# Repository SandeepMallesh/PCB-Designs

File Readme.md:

# PCB-Designs 

--------------------------------------------------------------------------------------------------------

** ALL PROJECTS ARE DESIGNED WITH KICAD ** : 𝕂𝕚𝕔𝕒𝕕

KICAD SOFTWARE LINK : 

** WINDOWS ** : https://www.kicad.org/download/windows/

** MAC OS **  : https://www.kicad.org/download/macos/

** LINUX **   : https://www.kicad.org/download/linux/

---------------------------------------------------------------------------------------------------------

𝕯𝖊𝖘𝖎𝖌𝖓𝖊𝖉 𝖇𝖞 ✍
✌𝓐𝓳𝓪𝔂𝓜𝓪𝓵𝓵𝓮𝓼𝓱✌
---------------------------------------------------------------------------------------------------------

███████████████████████████▀███████████████████████████████████
█▄─▄▄▀█▄─▄▄─█─▄▄▄▄█▄─▄█─▄▄▄▄█▄─▀█▄─▄█▄─▄▄─█▄─▄▄▀███▄─▄─▀█▄─█─▄█
██─██─██─▄█▀█▄▄▄▄─██─██─██▄─██─█▄▀─███─▄█▀██─██─████─▄─▀██▄─▄██
▀▄▄▄▄▀▀▄▄▄▄▄▀▄▄▄▄▄▀▄▄▄▀▄▄▄▄▄▀▄▄▄▀▀▄▄▀▄▄▄▄▄▀▄▄▄▄▀▀▀▀▄▄▄▄▀▀▀▄▄▄▀▀
███████████████████████████████████████████████████████████████████
██▀▄─████▄─▄██▀▄─██▄─█─▄█▄─▀█▀─▄██▀▄─██▄─▄███▄─▄███▄─▄▄─█─▄▄▄▄█─█─█
██─▀─██─▄█─███─▀─███▄─▄███─█▄█─███─▀─███─██▀██─██▀██─▄█▀█▄▄▄▄─█─▄─█
▀▄▄▀▄▄▀▄▄▄▀▀▀▄▄▀▄▄▀▀▄▄▄▀▀▄▄▄▀▄▄▄▀▄▄▀▄▄▀▄▄▄▄▄▀▄▄▄▄▄▀▄▄▄▄▄▀▄▄▄▄▄▀▄▀▄▀

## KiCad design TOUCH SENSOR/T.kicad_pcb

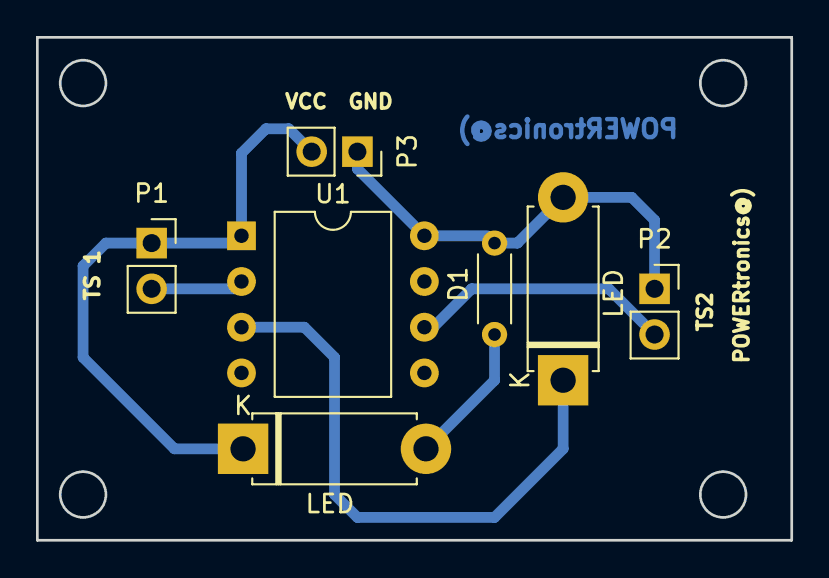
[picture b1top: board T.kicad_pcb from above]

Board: 2 copper layers, 41.9 x 27.9 mm, 7 parts (0 on the bottom side), 6 nets.

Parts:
D1: LED; D_5W_P10.16mm_Horizontal
LED: LED; D_5W_P10.16mm_Horizontal
LED#2: R; R_Axial_DIN0204_L3.6mm_D1.6mm_P5.08mm_Horizontal
P1, P2, P3: CONN_01X02; PinSocket_1x02_P2.54mm_Vertical
U1: NE555; DIP-8_W10.16mm

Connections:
GND: LED.1, P1.1, P3.2, U1.1
unnamed: D1.1, U1.3
unnamed: LED.2, LED#2.2
unnamed: P1.2, U1.2
unnamed: P2.2, U1.6
VCC: D1.2, LED#2.1, P2.1, P3.1, U1.8

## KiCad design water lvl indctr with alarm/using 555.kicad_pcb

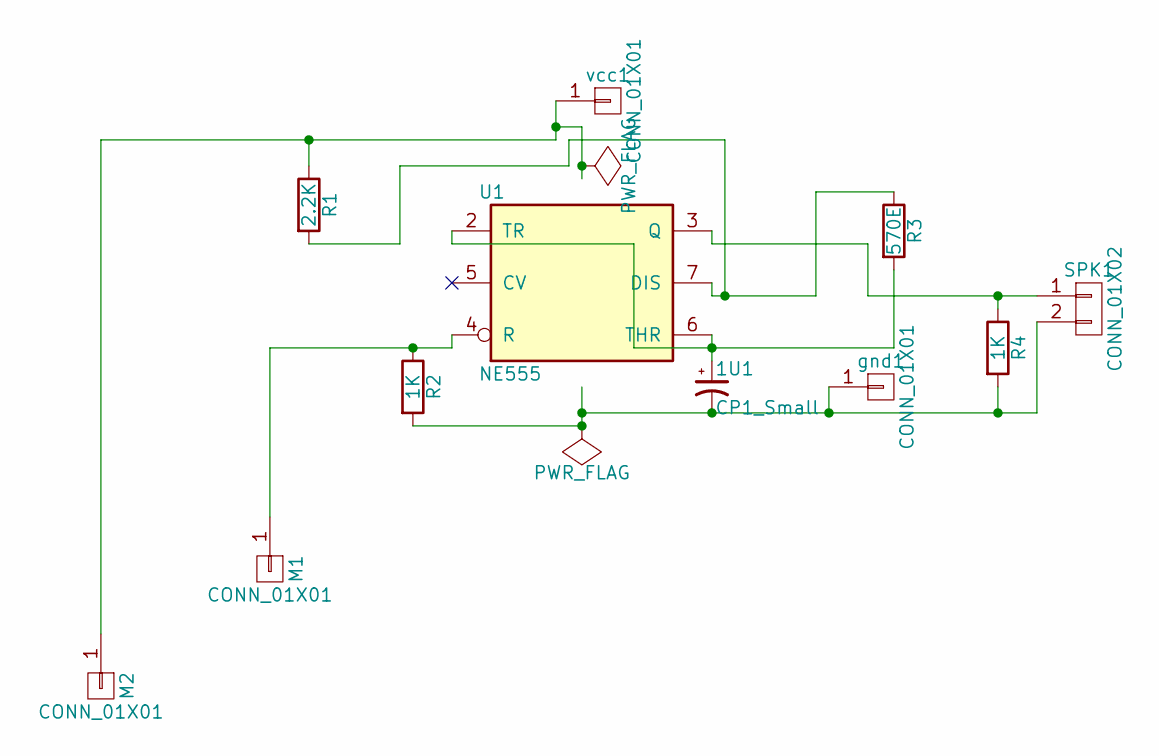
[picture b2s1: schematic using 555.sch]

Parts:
1U1: CP1_Small; C_Disc_D3.0mm_W1.6mm_P2.50mm
M1, M2: CONN_01X01; Pin_Header_Straight_1x01_Pitch2.54mm
R1: 2.2K; R_Axial_DIN0204_L3.6mm_D1.6mm_P5.08mm_Horizontal
R2, R4: 1K; R_Axial_DIN0204_L3.6mm_D1.6mm_P5.08mm_Horizontal
R3: 570E; R_Axial_DIN0204_L3.6mm_D1.6mm_P5.08mm_Horizontal
SPK1: CONN_01X02; Pin_Header_Straight_1x02_Pitch2.54mm
U1: NE555; DIP-8_W7.62mm
gnd1: CONN_01X01; Pin_Header_Straight_1x01_Pitch2.54mm
vcc1: CONN_01X01; Pin_Header_Straight_1x01_Pitch2.54mm

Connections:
GND: 1U1.2, R2.2, R4.2, SPK1.2, U1.1 (GND), gnd1.1
unnamed: 1U1.1, R3.2, U1.2 (TR), U1.6 (THR)
unnamed: M1.1, R2.1, U1.4 (R)
unnamed: R1.2, R3.1, U1.7 (DIS)
unnamed: R4.1, SPK1.1, U1.3 (Q)
VCC: M2.1, R1.1, U1.8 (VCC), vcc1.1

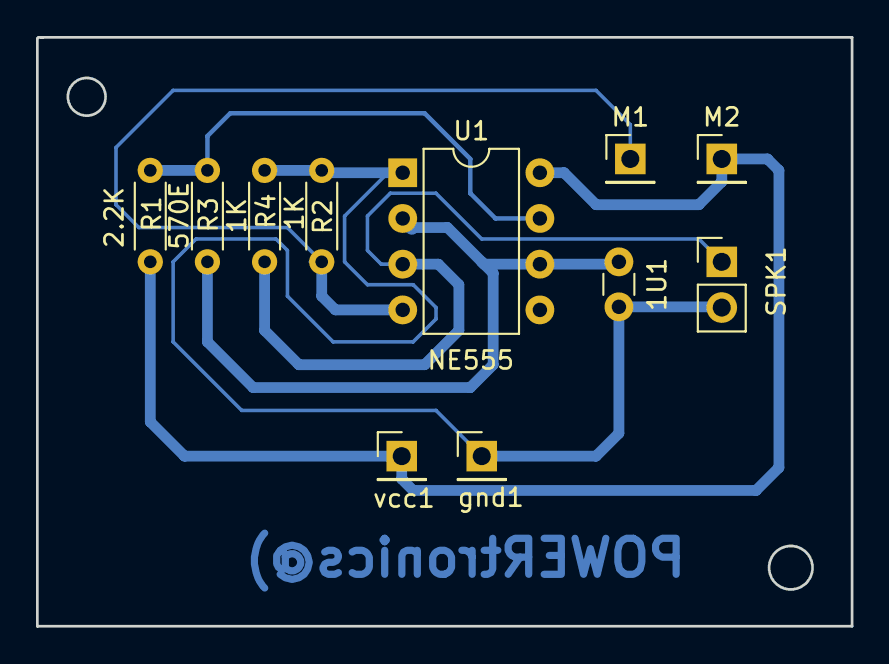
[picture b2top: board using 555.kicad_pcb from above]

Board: 2 copper layers, 45.3 x 32.7 mm, 11 parts (0 on the bottom side), 6 nets.

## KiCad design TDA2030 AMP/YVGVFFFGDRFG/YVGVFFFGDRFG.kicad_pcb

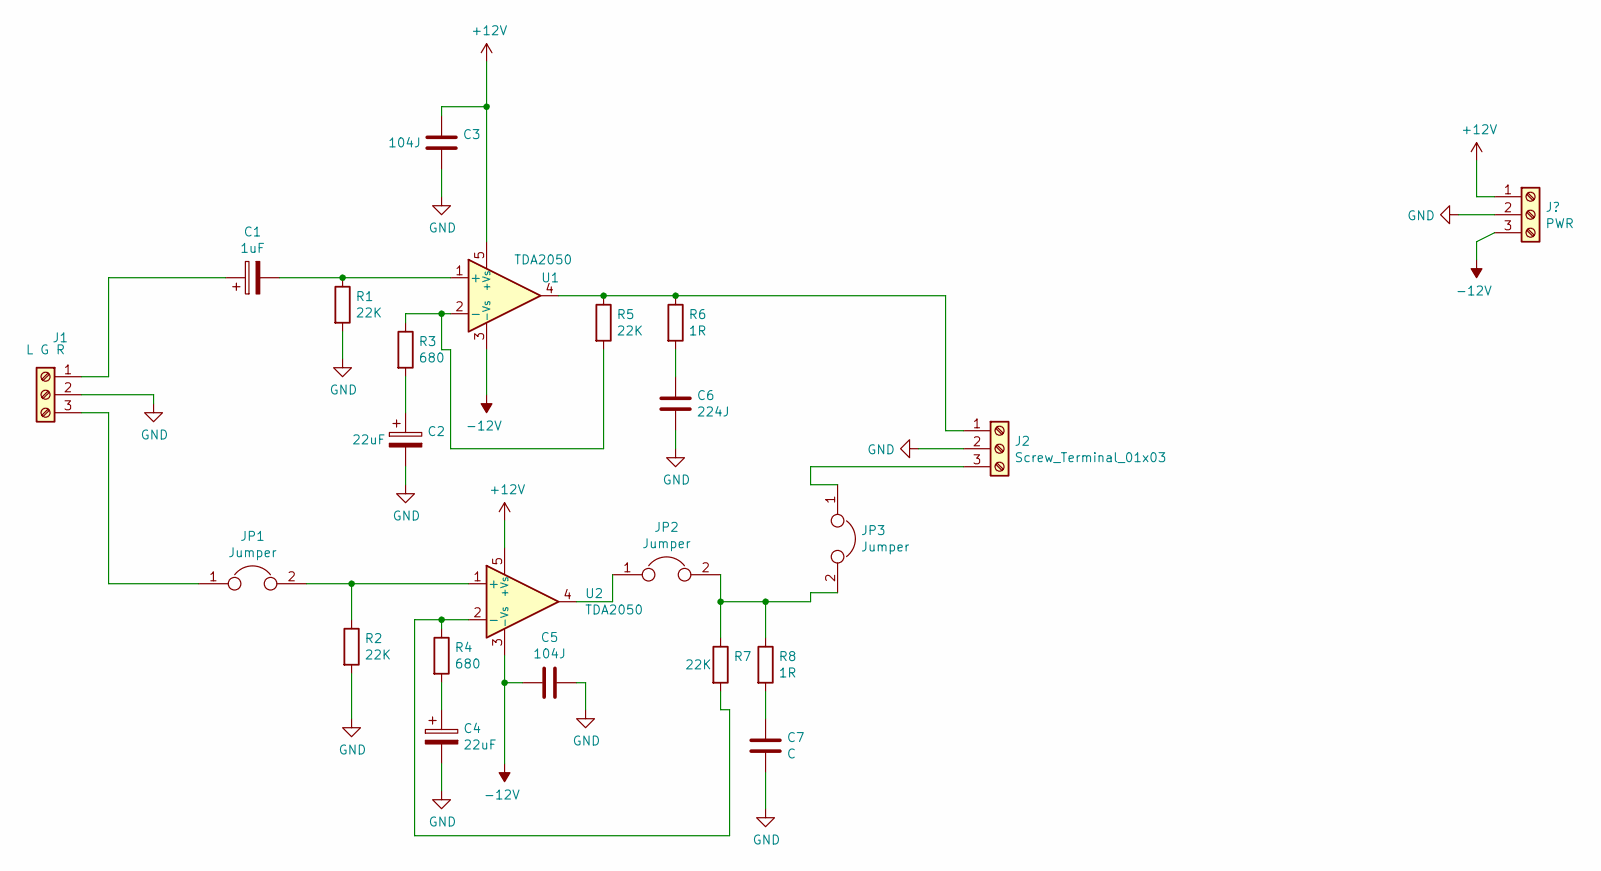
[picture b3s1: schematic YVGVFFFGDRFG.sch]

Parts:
C1: 1uF; CP_Radial_D4.0mm_P2.00mm
C2, C4: 22uF; CP_Radial_D4.0mm_P2.00mm
C3, C5: 104J; C_Rect_L4.6mm_W2.0mm_P2.50mm_MKS02_FKP02
C6: 224J; C_Rect_L4.6mm_W2.0mm_P2.50mm_MKS02_FKP02
C7: C; C_Rect_L4.0mm_W2.5mm_P2.50mm
J1: L G R; TerminalBlock_bornier-3_P5.08mm
J2: Screw_Terminal_01x03; TerminalBlock_bornier-3_P5.08mm
JP1, JP2, JP3: Jumper; TestPoint_2Pads_Pitch2.54mm_Drill0.8mm
R1, R2, R5, R7: 22K; R_Axial_DIN0204_L3.6mm_D1.6mm_P5.08mm_Horizontal
R3, R4: 680; R_Axial_DIN0204_L3.6mm_D1.6mm_P5.08mm_Horizontal
R6, R8: 1R; R_Axial_DIN0204_L3.6mm_D1.6mm_P5.08mm_Horizontal
U1, U2: TDA2050; TO-220-5_Vertical_StaggeredType1

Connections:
+12V: C3.1, U1.5 (+Vs), U2.5 (+Vs)
-12V: C5.2, U1.3 (-Vs), U2.3 (-Vs)
GND: C2.2, C3.2, C4.2, C5.1, C6.2, C7.2, J1.2, J2.2, R1.2, R2.2
unnamed: C1.1, J1.1
unnamed: C1.2, R1.1, U1.1 (+)
unnamed: C2.1, R3.2
unnamed: C4.1, R4.2
unnamed: C6.1, R6.2
unnamed: C7.1, R8.2
unnamed: J1.3, JP1.1
unnamed: J2.1, R5.1, R6.1, U1.4
unnamed: J2.3, JP3.1
unnamed: JP1.2, R2.1, U2.1 (+)
unnamed: JP2.1, U2.4
unnamed: JP2.2, JP3.2, R7.1, R8.1
unnamed: R3.1, R5.2, U1.2 (-)
unnamed: R4.1, R7.2, U2.2 (-)

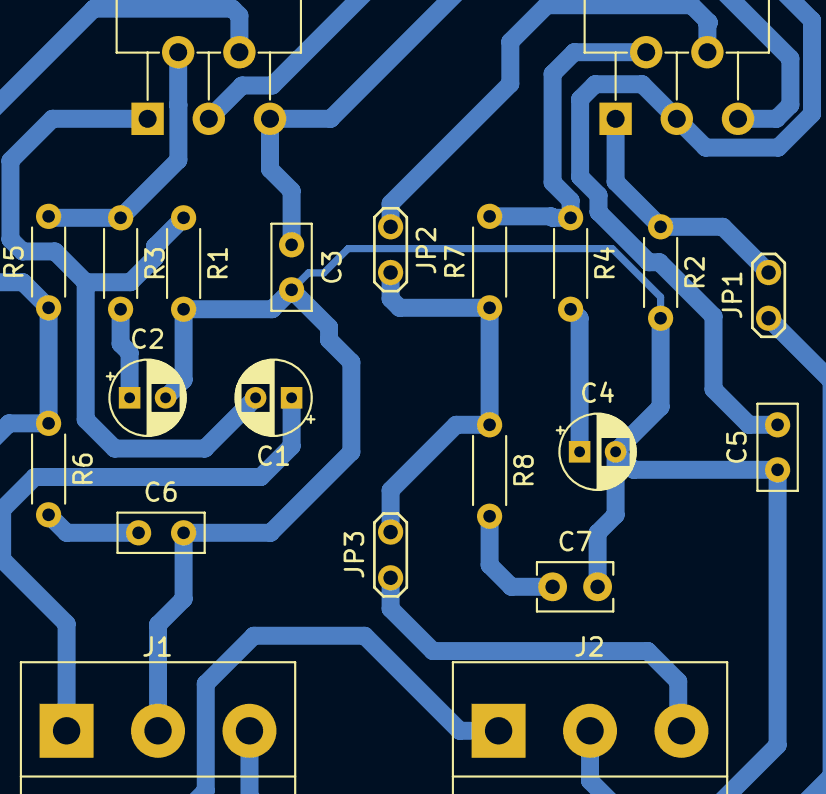
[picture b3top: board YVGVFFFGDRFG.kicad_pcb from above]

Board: 2 copper layers, 22 parts (0 on the bottom side), 17 nets.

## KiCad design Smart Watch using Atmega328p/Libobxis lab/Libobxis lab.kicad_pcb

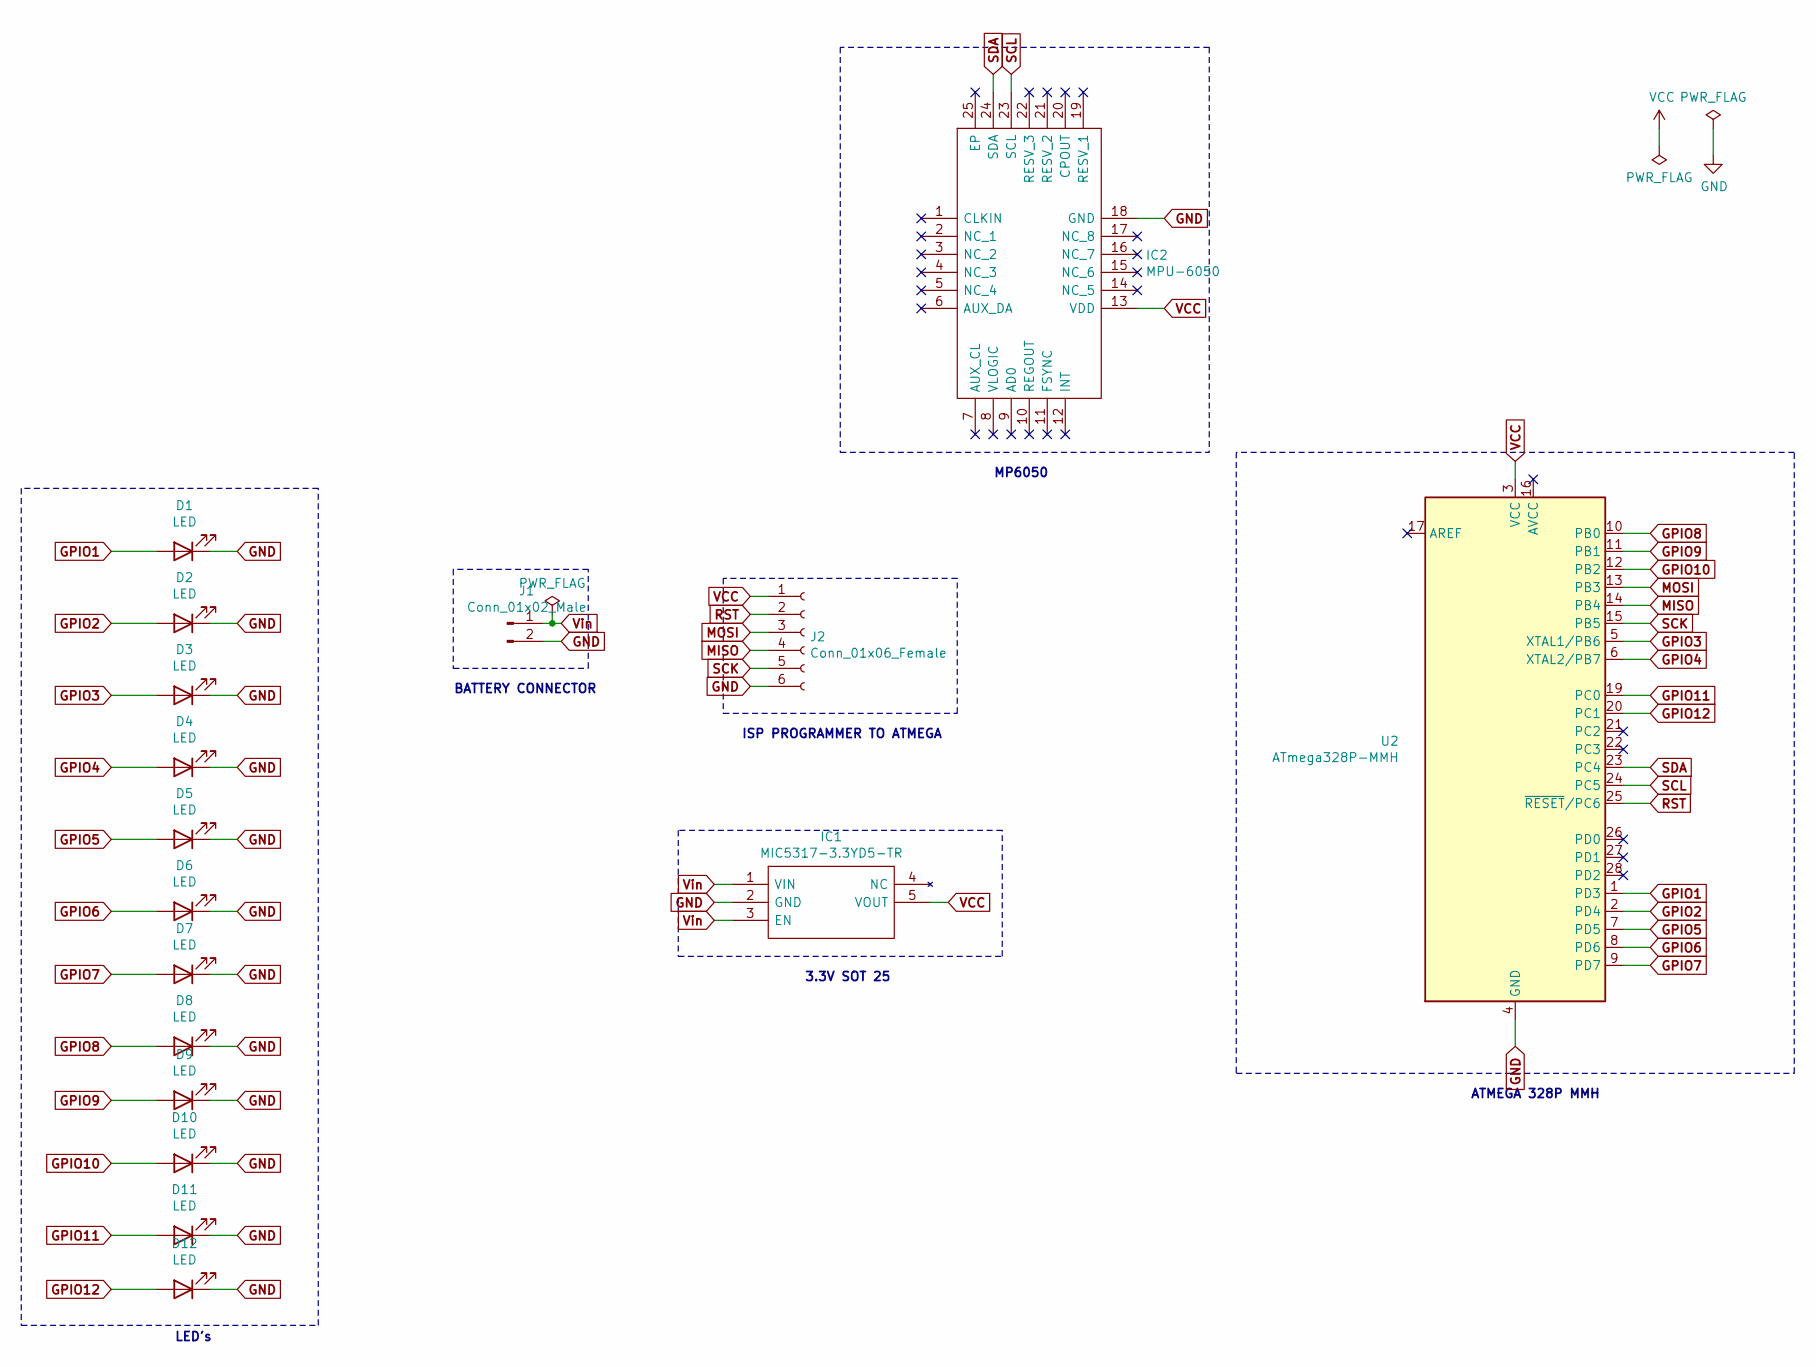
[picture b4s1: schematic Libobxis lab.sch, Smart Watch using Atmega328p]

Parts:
D1, D2, D3, D4, D5, D6, D7, D8, D9, D10, D11, D12: LED; LED_0805
IC1: MIC5317-3.3YD5-TR; SOT95P280X145-5N; Manufacturer_Part_Number MIC5317-3.3YD5-TR; Mouser Part Number 998-MIC5317-3.3YD5TR
IC2: MPU-6050; MPU6050; Manufacturer_Part_Number MPU-6050; Mouser Part Number 410-MPU-6050
J1: Conn_01x02_Male; PinHeader_1x02_P2.54mm_Vertical
J2: Conn_01x06_Female; PinHeader_1x06_P2.00mm_Vertical
U2: ATmega328P-MMH; QFN45P400X400X100-29N-D

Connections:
GND: D1.1 (K), D2.1 (K), D3.1 (K), D4.1 (K), D5.1 (K), D6.1 (K), D7.1 (K), D8.1 (K), D9.1 (K), D10.1 (K), D11.1 (K), D12.1 (K), IC1.2 (GND), IC2.18 (GND), J1.2, J2.6, U2.4 (GND), U2.18 (GND), U2.29 (GND)
GPIO1: D1.2 (A), U2.1 (PD3)
GPIO2: D2.2 (A), U2.2 (PD4)
GPIO3: D3.2 (A), U2.5 (XTAL1/PB6)
GPIO4: D4.2 (A), U2.6 (XTAL2/PB7)
GPIO5: D5.2 (A), U2.7 (PD5)
GPIO6: D6.2 (A), U2.8 (PD6)
GPIO7: D7.2 (A), U2.9 (PD7)
GPIO8: D8.2 (A), U2.10 (PB0)
GPIO9: D9.2 (A), U2.11 (PB1)
GPIO10: D10.2 (A), U2.12 (PB2)
GPIO11: D11.2 (A), U2.19 (PC0)
GPIO12: D12.2 (A), U2.20 (PC1)
MISO: J2.4, U2.14 (PB4)
MOSI: J2.3, U2.13 (PB3)
RST: J2.2, U2.25 (~RESET~/PC6)
SCK: J2.5, U2.15 (PB5)
SCL: IC2.23 (SCL), U2.24 (PC5)
SDA: IC2.24 (SDA), U2.23 (PC4)
VCC: IC1.5 (VOUT), IC2.13 (VDD), J2.1, U2.3 (VCC)
Vin: IC1.1 (VIN), IC1.3 (EN), J1.1

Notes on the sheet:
3.3V SOT 25
ISP PROGRAMMER TO ATMEGA
BATTERY CONNECTOR
LED's
ATMEGA 328P MMH
MP6050

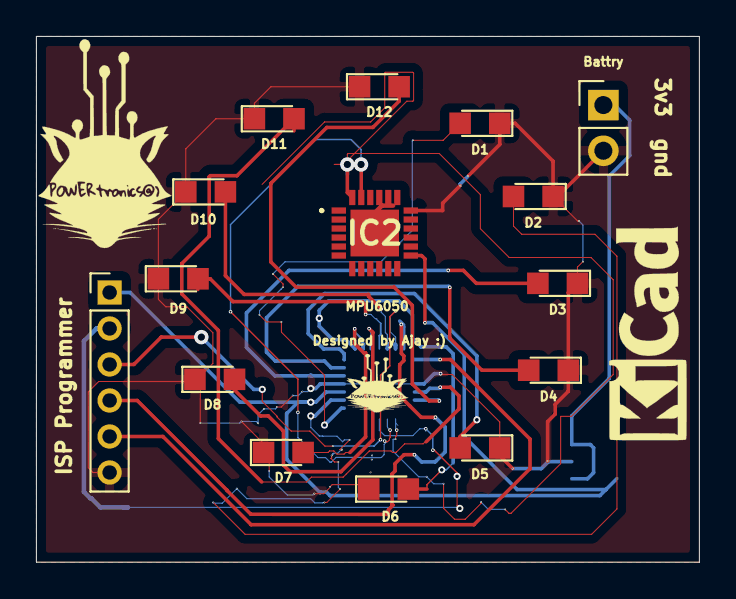
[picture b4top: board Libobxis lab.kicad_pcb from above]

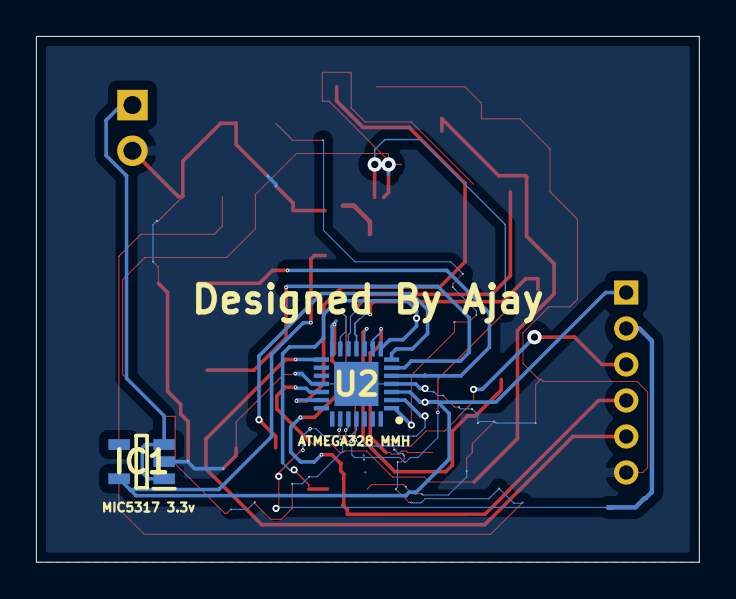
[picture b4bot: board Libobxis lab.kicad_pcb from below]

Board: 2 copper layers, 36.8 x 29.2 mm, 17 parts (2 on the bottom side), 21 nets.

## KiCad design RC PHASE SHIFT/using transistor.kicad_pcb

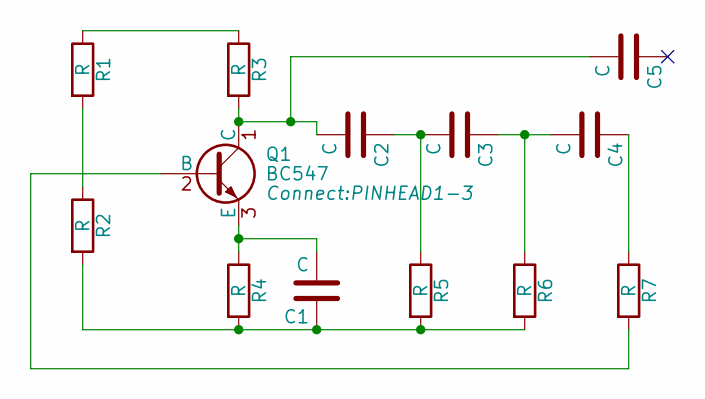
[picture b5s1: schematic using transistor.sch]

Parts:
C1, C2, C3, C4, C5: C; C_Disc_D3.0mm_W1.6mm_P2.50mm
Q1: BC547; PINHEAD1-3
R1, R2, R3, R4, R5, R6, R7: R; Resistor_Horizontal_RM7mm

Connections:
unnamed: C1.1, R2.2, R4.2, R5.2, R6.2
unnamed: C1.2, Q1.3 (E), R4.1
unnamed: C2.1, C3.2, R5.1
unnamed: C2.2, C5.2, Q1.1 (C), R3.2
unnamed: C3.1, C4.2, R6.1
unnamed: C4.1, R7.1
unnamed: Q1.2 (B), R7.2
unnamed: R1.1, R3.1
unnamed: R1.2, R2.1

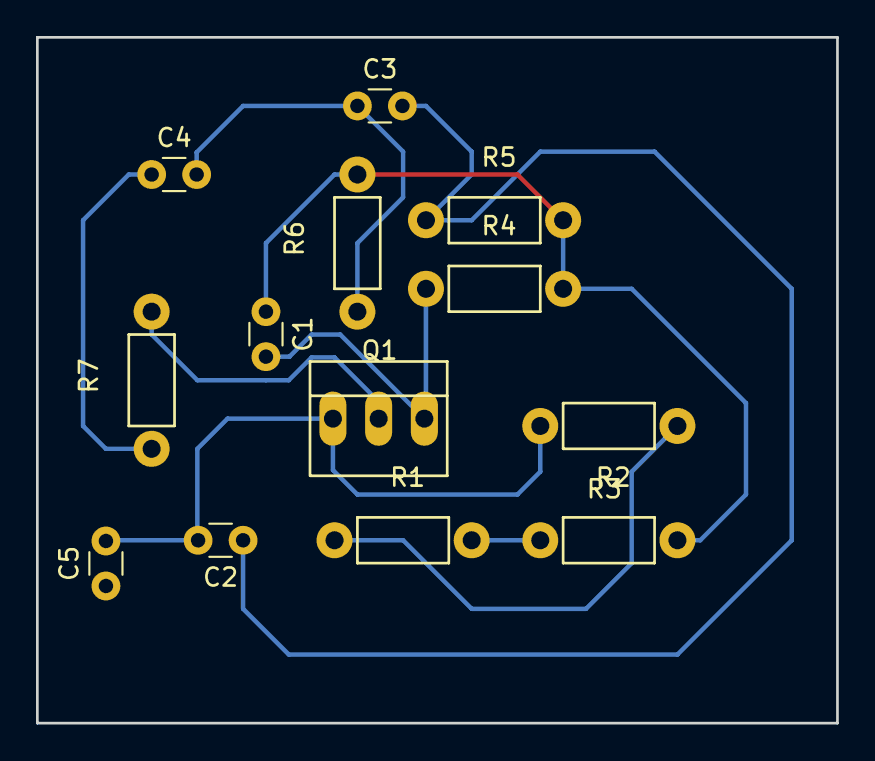
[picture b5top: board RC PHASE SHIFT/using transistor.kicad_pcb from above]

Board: 2 copper layers, 44.5 x 38.1 mm, 13 parts (0 on the bottom side), 9 nets.

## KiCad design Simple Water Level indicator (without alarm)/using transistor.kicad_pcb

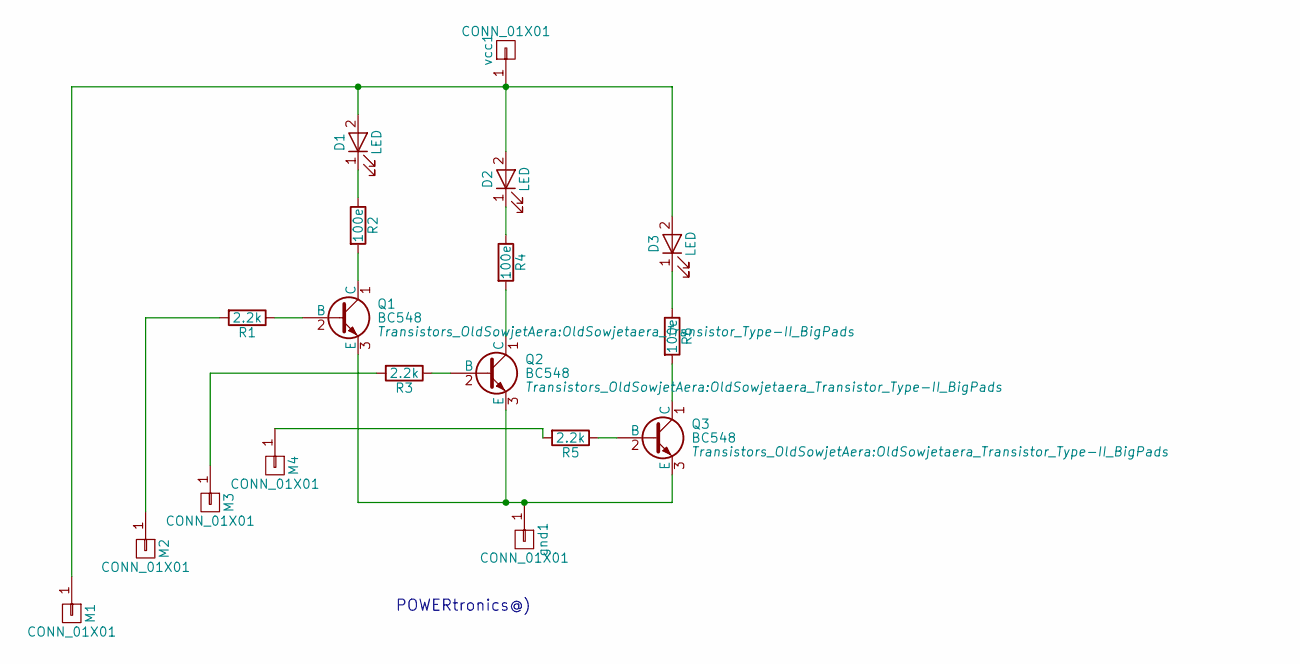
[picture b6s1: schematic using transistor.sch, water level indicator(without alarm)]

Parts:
D1, D2, D3: LED; LED_D3.0mm_FlatTop
M1, M2, M3, M4: CONN_01X01; Pin_Header_Straight_1x01_Pitch1.00mm
Q1, Q2, Q3: BC548; OldSowjetaera_Transistor_Type-II_BigPads
R1, R3, R5: 2.2k; Resistor_Horizontal_RM7mm
R2, R4, R6: 100e; Resistor_Horizontal_RM7mm
gnd1: CONN_01X01; Pin_Header_Straight_1x01_Pitch1.00mm
vcc1: CONN_01X01; Pin_Header_Straight_1x01_Pitch1.00mm

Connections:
unnamed: D1.1 (K), R2.1
unnamed: D1.2 (A), D2.2 (A), D3.2 (A), M1.1, vcc1.1
unnamed: D2.1 (K), R4.1
unnamed: D3.1 (K), R6.1
unnamed: M2.1, R1.2
unnamed: M3.1, R3.2
unnamed: M4.1, R5.2
unnamed: Q1.1 (C), R2.2
unnamed: Q1.2 (B), R1.1
unnamed: Q1.3 (E), Q2.3 (E), Q3.3 (E), gnd1.1
unnamed: Q2.1 (C), R4.2
unnamed: Q2.2 (B), R3.1
unnamed: Q3.1 (C), R6.2
unnamed: Q3.2 (B), R5.1

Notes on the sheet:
POWERtronics@)

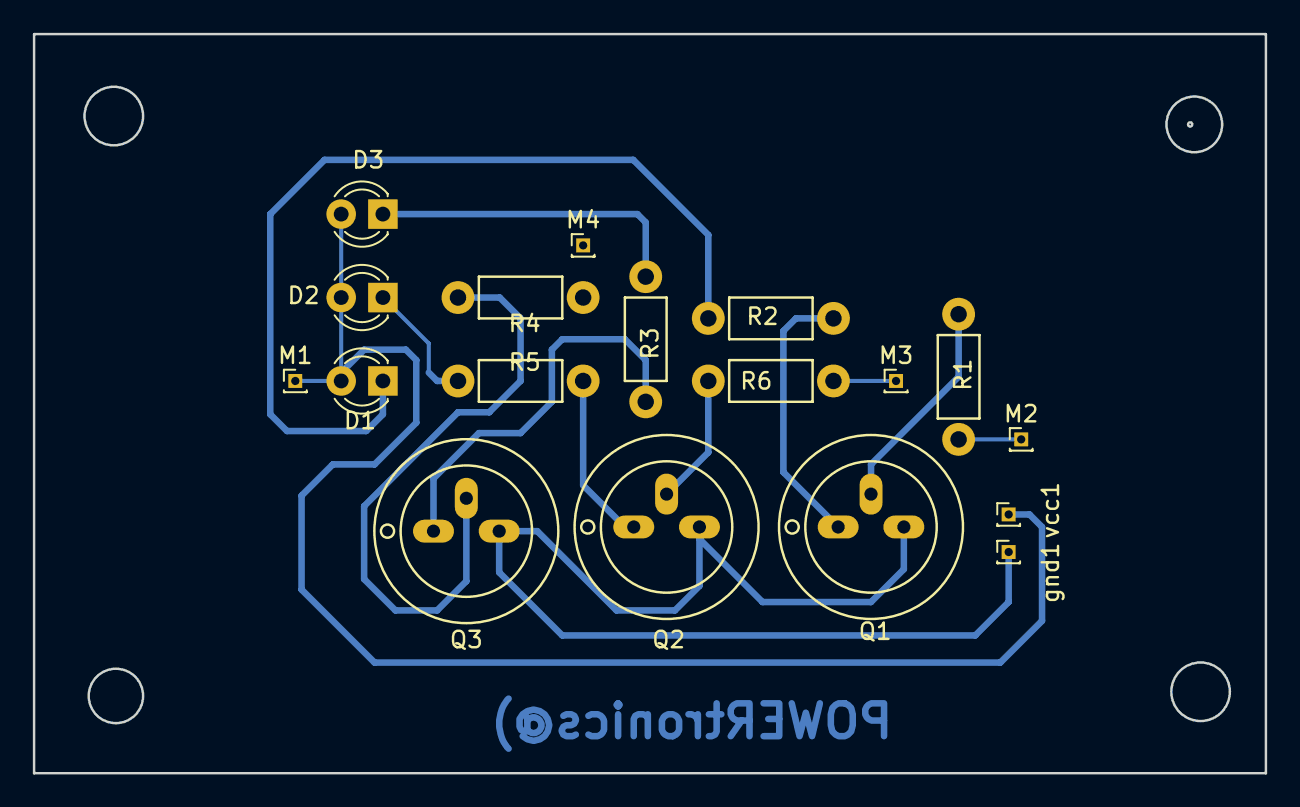
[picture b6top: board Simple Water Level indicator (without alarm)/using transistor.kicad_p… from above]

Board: 2 copper layers, 75.0 x 45.0 mm, 18 parts (0 on the bottom side), 14 nets.

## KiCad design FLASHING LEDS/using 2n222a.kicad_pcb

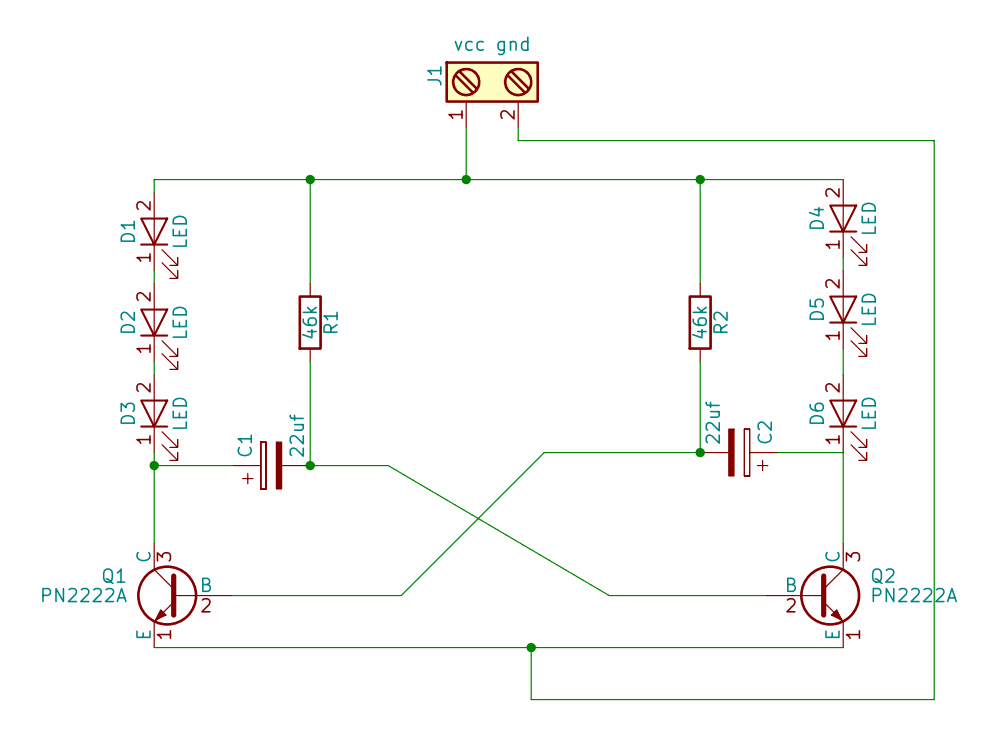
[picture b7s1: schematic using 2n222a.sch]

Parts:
C1, C2: 22uf; C_Radial_D6.3_L11.2_P2.5
D1, D2, D3, D4, D5, D6: LED; LED_D5.0mm
J1: vcc gnd; bornier2
Q1, Q2: PN2222A; TO-92_Inline_Wide
R1, R2: 46k; Resistor_Horizontal_RM7mm

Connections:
unnamed: C1.1, D3.1 (K), Q1.3 (C)
unnamed: C1.2, Q2.2 (B), R1.2
unnamed: C2.1, D6.1 (K), Q2.3 (C)
unnamed: C2.2, Q1.2 (B), R2.2
unnamed: D1.1 (K), D2.2 (A)
unnamed: D1.2 (A), D4.2 (A), J1.1, R1.1, R2.1
unnamed: D2.1 (K), D3.2 (A)
unnamed: D4.1 (K), D5.2 (A)
unnamed: D5.1 (K), D6.2 (A)
unnamed: J1.2, Q1.1 (E), Q2.1 (E)

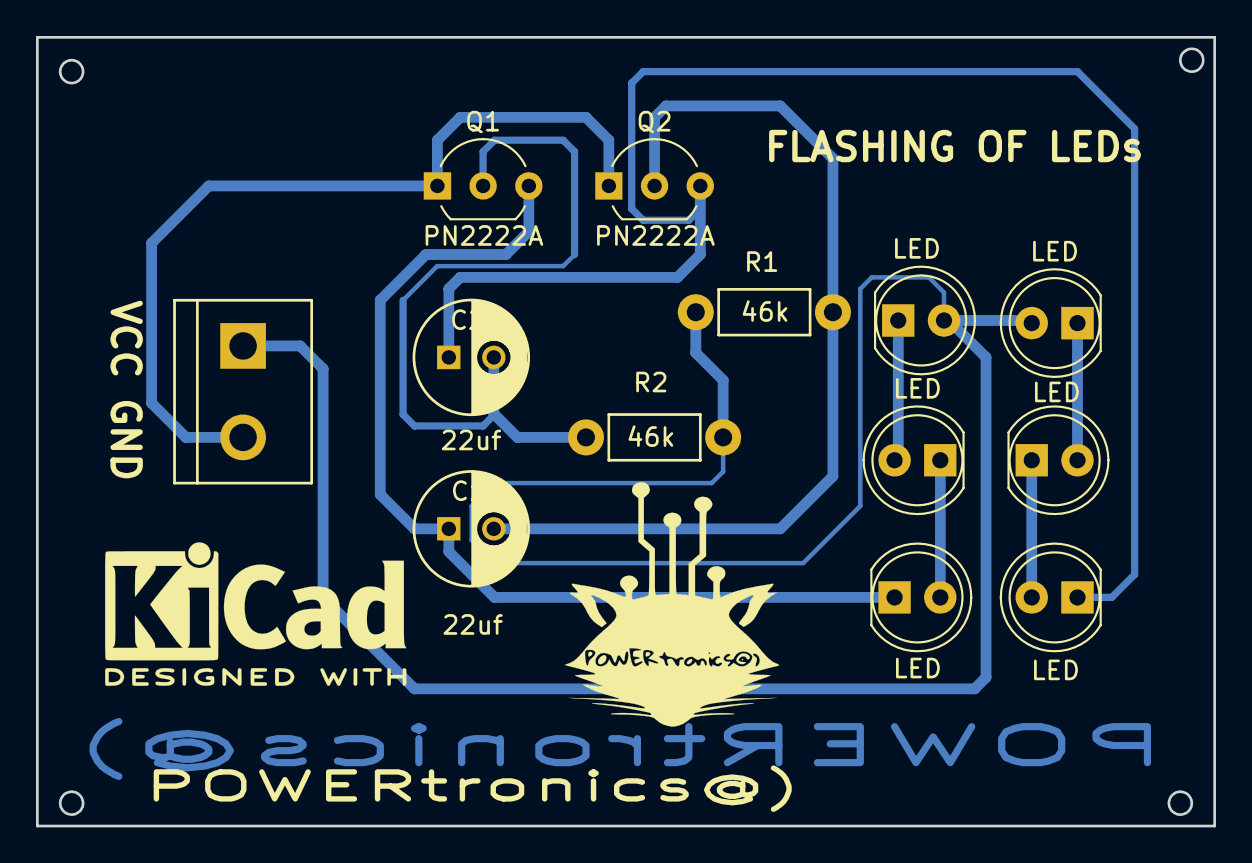
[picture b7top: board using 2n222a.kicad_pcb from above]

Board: 2 copper layers, 65.4 x 43.8 mm, 13 parts (0 on the bottom side), 10 nets.

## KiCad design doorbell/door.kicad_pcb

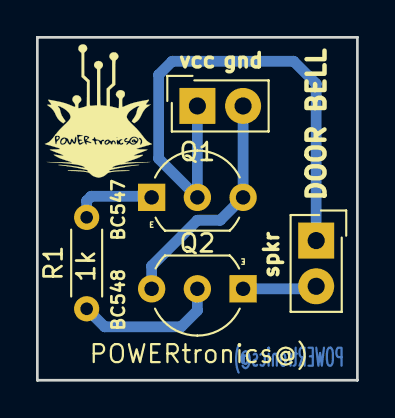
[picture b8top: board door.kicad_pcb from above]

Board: 2 copper layers, 17.8 x 19.0 mm, 5 parts (0 on the bottom side), 5 nets.

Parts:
P1, P2: CONN_01X02; SDL-102-X-XX_2x01
Q1: BC547; TO-92_Inline_Wide
Q2: BC548; TO-92_Inline_Wide
R1: 1k; R_Axial_DIN0204_L3.6mm_D1.6mm_P5.08mm_Horizontal

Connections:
unnamed: P1.1, P2.1, Q1.2
unnamed: P1.2, Q1.3, Q2.3
unnamed: P2.2, Q2.1
unnamed: Q1.1, R1.2
unnamed: Q2.2, R1.1

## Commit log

2023-09-06 PCB Designs
2023-09-06 test
